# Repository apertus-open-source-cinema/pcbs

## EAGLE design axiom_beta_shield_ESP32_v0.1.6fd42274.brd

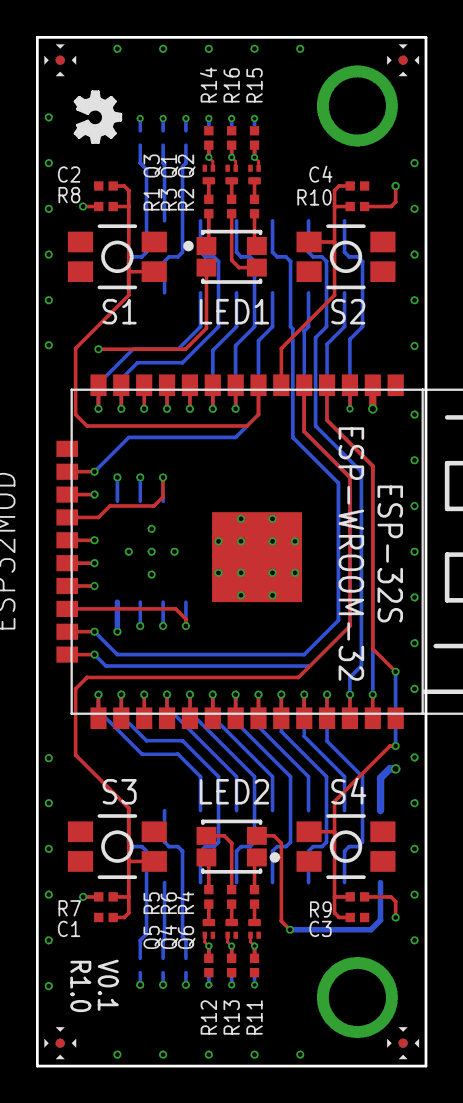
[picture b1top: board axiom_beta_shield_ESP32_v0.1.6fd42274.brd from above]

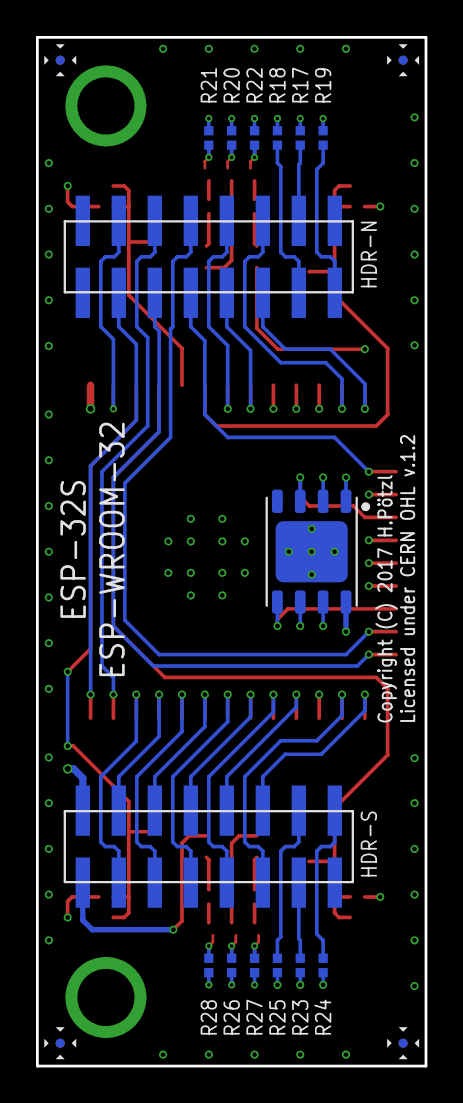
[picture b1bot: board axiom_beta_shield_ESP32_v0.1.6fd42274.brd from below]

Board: 4 copper layers, 21.6 x 57.1 mm, 49 parts (15 on the bottom side), 61 nets.

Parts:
C1, C2, C3, C4: 0402-C
HDR-N: 2X08M_SMD
HDR-S: 2X08M_SMD
LED1, LED2: RGBLED_PLCC4
LOGO1: OSHW_LOGO_FILLX0100-NT; OSHW_FILLX100_NOTEXT
Q1, Q2, Q3, Q4, Q5, Q6: PMZB290UNE; SOT883(B)
R1, R2, R3, R4, R5, R6, R7, R8, R9, R10, R11, R12, R13, R14, R15, R16, R17, R18, R19, R20, R21, R22, R23, R24, R25, R26, R27, R28: 0402-C
S1, S2, S3, S4: DTSM-6; 3X4MM
U1: ESP32MOD
U$1: IS25LP128; WSON127P600X500-8N

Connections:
B1: Q1.3, R3.1
B2: Q4.3, R6.1
G1: Q2.3, R2.1
G2: Q5.3, R5.1
GND: C1.2, C2.2, C3.2, C4.2, HDR-N.1, HDR-N.2, Q1.2, Q2.2, Q3.2, Q4.2, Q5.2, Q6.2, R11.1, R12.1, R13.1, R14.1, R15.1, R16.1, S1.1, S2.1, S3.1, S4.1, U1.0, U1.1, U1.15, U1.38, U$1.4, U$1.PAD
LED1_B: R20.2, U1.11
LED1_G: R21.2, U1.12
LED1_R: R22.2, U1.10
LED2_R: R28.2, U1.27
unnamed: LED1.1, R1.2
unnamed: LED1.4, R2.2
unnamed: LED1.3, R3.2
unnamed: LED2.1, R4.2
unnamed: LED2.4, R5.2
unnamed: LED2.3, R6.2
unnamed: Q3.1, R14.2, R19.1, R22.1
unnamed: Q2.1, R15.2, R18.1, R21.1
unnamed: Q1.1, R16.2, R17.1, R20.1
unnamed: Q4.1, R13.2, R23.1, R26.1
unnamed: Q5.1, R12.2, R24.1, R27.1
unnamed: Q6.1, R11.2, R25.1, R28.1
R1: Q3.3, R1.1
R2: Q6.3, R4.1
S1: C2.1, R8.1, S1.4, U1.7
S2: C4.1, R10.1, S2.4, U1.6
S3: C1.1, R7.1, S3.4, U1.5
S4: C3.1, R9.1, S4.4, U1.4
SH_N_IO0: HDR-N.12, U1.13
SH_N_IO1: HDR-N.11, U1.14
SH_N_IO2: HDR-N.10, U1.8
SH_N_IO3: HDR-N.9, U1.9
SH_N_IO4: HDR-N.8, U1.23
SH_N_IO5: HDR-N.7, U1.16
SH_N_IO6: HDR-N.6, U1.36
SH_N_IO7: HDR-N.5, U1.24
SH_N_IO8: HDR-N.4, U1.3
SH_N_IO9: HDR-N.3, R27.2, U1.37
SH_S_IO0: HDR-S.12, U1.25
SH_S_IO1: HDR-S.11, U1.26
SH_S_IO2: HDR-S.10, R26.2, U1.28
SH_S_IO3: HDR-S.9, U1.29
SH_S_IO4: HDR-S.8, U1.30
SH_S_IO5: HDR-S.7, U1.31
SH_S_IO6: HDR-S.6, U1.32
SH_S_IO7: HDR-S.5, U1.33
SH_S_IO8: HDR-S.4, U1.34
SH_S_IO9: HDR-S.3, U1.35
SPI: U1.22, U$1.5
SPICLK: U1.20, U$1.6
SPICS0: U1.19, U$1.1
SPIHD: U1.17, U$1.7
SPIQ: U1.21, U$1.2
SPIWP: U1.18, U$1.3
VCC: HDR-S.2, R7.2, R8.2, R9.2, R10.2, U1.2, U$1.8
VDD: HDR-S.1, LED1.2, LED2.2
XX1_N: HDR-N.14, R17.2
XX2_N: HDR-N.13, R18.2
XX2_P: HDR-N.15, R19.2
XX3_P: HDR-S.13, R23.2
XX4_N: HDR-S.16, R24.2
XX4_P: HDR-S.14, R25.2

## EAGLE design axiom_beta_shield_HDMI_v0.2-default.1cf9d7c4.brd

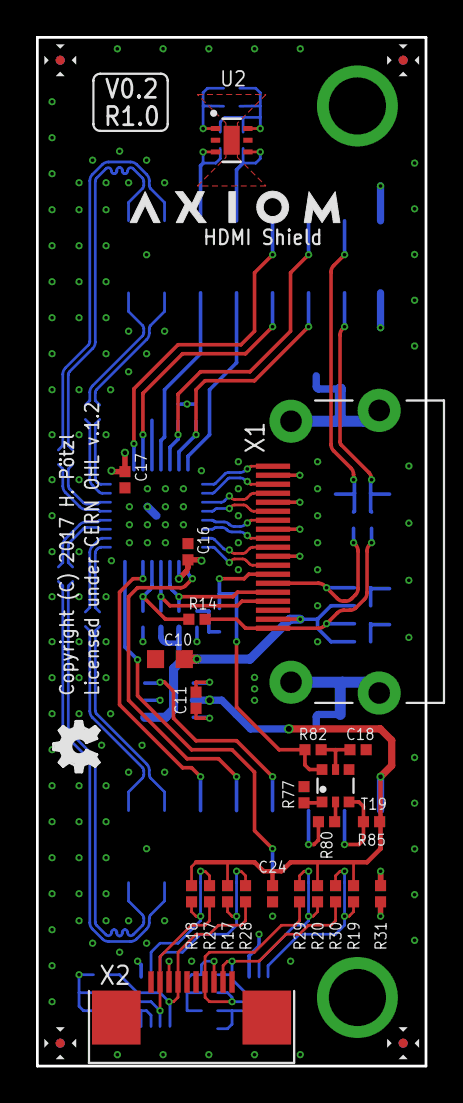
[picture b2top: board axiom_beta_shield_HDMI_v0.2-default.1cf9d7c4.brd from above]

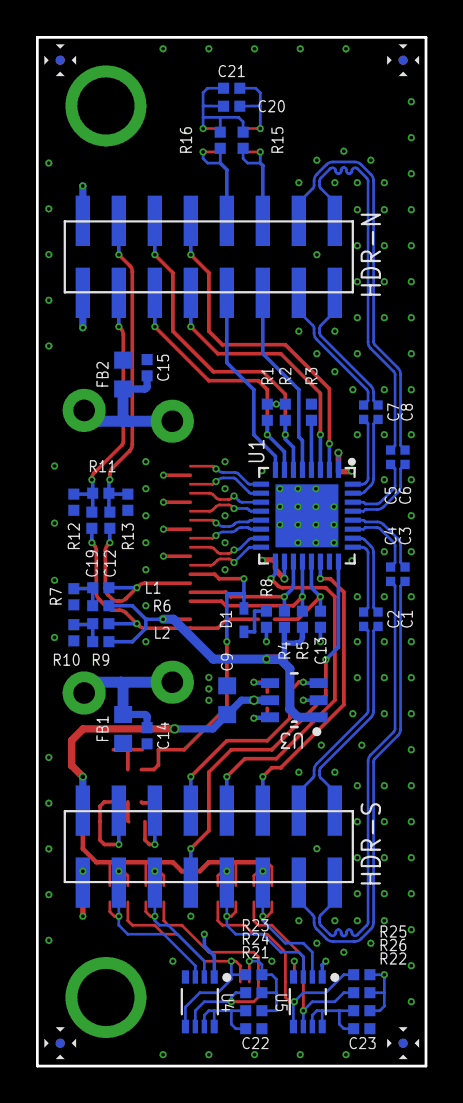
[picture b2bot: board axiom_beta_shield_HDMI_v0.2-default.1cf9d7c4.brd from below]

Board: 4 copper layers, 21.6 x 57.1 mm, 76 parts (50 on the bottom side), 73 nets.

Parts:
C1, C2, C3, C4, C5, C6, C7, C8: 100n; 0402-C
C9: 2u2; 0603-B
C10: 10u; 0603-B
C11: 220n; 0402-B
C12, C19: 0402-B
C13: 1-10n; 0402-B
C14, C15: 10n; 0402-B
C16, C17, C20, C22, C23: 100n; 0402-B
C18: 47p; 0402-B
C21, C24: 10u; 0402-B
D1: SOD523
FB1, FB2: 0603-B
HDR-N: 2X08M_SMD
HDR-S: 2X08M_SMD
L1, L2: 0402-B
LOGO1: OSHW_LOGO_FILLX0100-NT; OSHW_FILLX100_NOTEXT
R1, R2, R4, R5: 2k2; 0402-B
R3: 12k4; 0402-B
R6, R7, R8, R9, R10, R11, R12, R13, R14: 0402-B
R15, R16: 1k; 0402-B
R17, R18, R19, R20, R21, R22, R23, R24, R25, R26: 4k7; 0402-B
R27, R28, R29, R30: 100R; 0402-B
R31: 0R; 0402-B
R77: 100; 0402-B
R80: 10k; 0402-B
R82: 1M; 0402-B
R85: 100k; 0402-B
T19: PMBT3904SY; SOT363
U1: PTN3363; HVQFN32
U2: NOA1305; CUDFN6
U3: REG710-DBV; DBV
U4, U5: GTL2002DC; VSSOP-8
U$1: AXIOM_LOGO459X70; AXIOM_LOGO_459X70
X1: HDMI-10029449; 10029449-X01XLF
X2: 68711014022

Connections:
3V3: C9.1, C16.1, C17.1, C20.1, C21.1, C24.1, HDR-S.2, R1.1, R2.1, R8.1, R15.1, R16.1, R17.1, R18.1, R19.1, R20.1, R85.2, U1.1, U1.18, U2.6, U3.5, U4.1, U5.1
5V0: C10.1, R4.1, R5.1, R6.1, R9.1, U3.1, X1.18
CLOCK_N: U1.16, X1.12
CLOCK_P: U1.15, X1.10
DATA0_N: U1.14, X1.9
DATA0_P: U1.13, X1.7
DATA1_N: U1.12, X1.6
DATA1_P: U1.11, X1.4
DATA2_N: U1.10, X1.3
DATA2_P: U1.9, X1.1
GND: C9.2, C10.2, C13.2, C14.2, C15.2, C16.2, C17.2, C18.2, C20.2, C21.2, C22.2, C23.2, C24.2, FB1.2, FB2.2, HDR-N.1, HDR-N.2, R3.2, R7.2, R10.2, R12.2, R13.2, R77.1, T19.4, U1.EP, U2.1, U3.2, U4.4, U5.4, X1.2, X1.5, X1.8, X1.11, X1.17, X2.1, X2.5, X2.6, X2.10
HDMI_CEC: D1.C, R82.2, T19.6, X1.13
HDMI_SCL: R4.2, U1.19, X1.15
HDMI_SDA: R5.2, U1.20, X1.16
HEAC+: C12.1, L1.1, X1.14
HEAC-: C19.1, L2.1, R14.2, X1.19
HPD: C13.1, R14.1, U1.21
IN_D1_N: C2.1, U1.25
IN_D1_P: C1.1, U1.26
IN_D2_N: C4.1, U1.27
IN_D2_P: C3.1, U1.28
IN_D3_N: C6.1, U1.29
IN_D3_P: C5.1, U1.30
IN_D4_N: C8.1, U1.31
IN_D4_P: C7.1, U1.32
unnamed: L1.2, R6.2, R7.1
unnamed: L2.2, R9.2, R10.1
unnamed: C22.1, R21.2, U4.7, U4.8
unnamed: C23.1, R22.2, U5.7, U5.8
unnamed: C15.1, FB2.1, X1.Z3, X1.Z4
unnamed: C11.1, U3.6
unnamed: C11.2, U3.4
unnamed: C14.1, FB1.1, X1.Z1, X1.Z2
unnamed: R3.1, U1.4
unnamed: D1.A, R8.2
unnamed: R77.2, T19.1
unnamed: C18.1, R82.1, T19.5
unnamed: R80.1, T19.2
SH_N_IO0: HDR-N.12, R15.2, U2.3
SH_N_IO1: HDR-N.11, U1.5
SH_N_IO2: HDR-N.10, R16.2, U2.4
SH_N_IO3: HDR-N.9, U1.8
SH_N_IO4: HDR-N.8, U1.2
SH_N_IO5: HDR-N.7, U1.3
SH_N_IO6: HDR-N.6, R2.2, U1.6
SH_N_IO7: HDR-N.5, R1.2, U1.7
SH_N_IO8: C12.2, HDR-N.4, R11.1, R13.1
SH_N_IO9: C19.2, HDR-N.3, R11.2, R12.1
SH_S_IO0: HDR-S.12, U1.22
SH_S_IO1: HDR-S.11, R18.2, R27.1, U5.2
SH_S_IO2: HDR-S.10, U1.17
SH_S_IO3: HDR-S.9, R17.2, R28.1, U5.3
SH_S_IO4: HDR-S.8, U3.3
SH_S_IO5: HDR-S.7, U1.24
SH_S_IO6: HDR-S.6, R80.2
SH_S_IO7: HDR-S.5, R20.2, R29.1, U4.2
SH_S_IO8: HDR-S.4, R85.1, T19.3
SH_S_IO9: HDR-S.3, R19.2, R30.1, U4.3
S_IO1: R26.2, R27.2, U5.6, X2.2
S_IO3: R25.2, R28.2, U5.5, X2.4
S_IO7: R24.2, R29.2, U4.6, X2.7
S_IO9: R23.2, R30.2, U4.5, X2.9
VDD: HDR-S.1, R31.2
VIO13: R22.1, R25.1, R26.1, X2.3
VIO79: R21.1, R23.1, R24.1, R31.1, X2.8
XX1_N: C6.2, HDR-N.14
XX1_P: C5.2, HDR-N.16
XX2_N: C7.2, HDR-N.13
XX2_P: C8.2, HDR-N.15
XX3_N: C4.2, HDR-S.15
XX3_P: C3.2, HDR-S.13
XX4_N: C1.2, HDR-S.16
XX4_P: C2.2, HDR-S.14

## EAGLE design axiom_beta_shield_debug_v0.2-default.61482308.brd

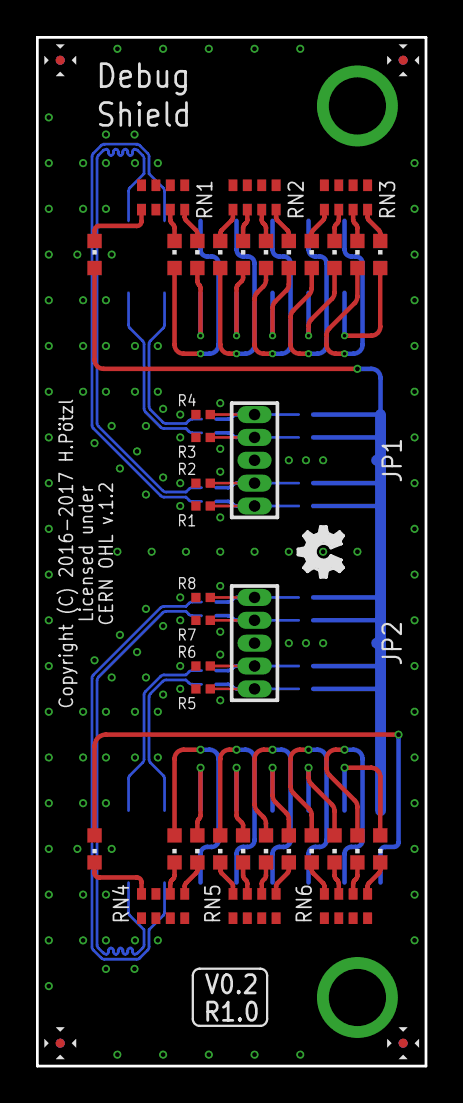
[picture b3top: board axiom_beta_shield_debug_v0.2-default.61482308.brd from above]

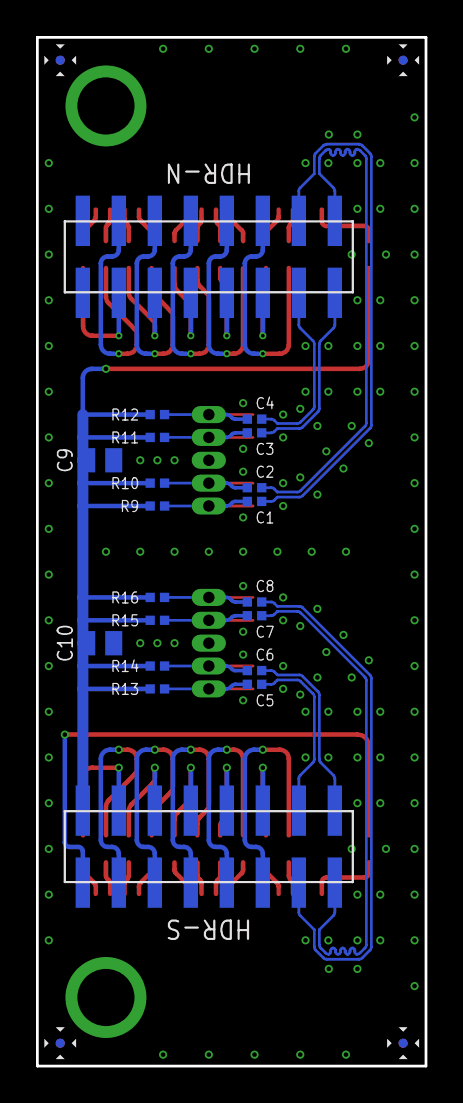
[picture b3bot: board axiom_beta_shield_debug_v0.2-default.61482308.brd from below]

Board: 4 copper layers, 21.6 x 57.1 mm, 59 parts (20 on the bottom side), 61 nets.

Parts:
C1, C2, C3, C4, C5, C6, C7, C8: 0402-C
C9, C10: 0805-C
HDR-N: 2X08M_SMD
HDR-S: 2X08M_SMD
JP1, JP2: 1X05U
LED1, LED2, LED3, LED4, LED5, LED6, LED7, LED8, LED9, LED10, LED11, LED12, LED13, LED14, LED15, LED16, LED17, LED18, LED19, LED20, LED21, LED22: CHIPLED_0603
LOGO1: OSHW_LOGO_FILLX0100-NT; OSHW_FILLX100_NOTEXT
R1, R2, R3, R4, R5, R6, R7, R8, R9, R10, R11, R12, R13, R14, R15, R16: 0402-C
RN1, RN2, RN3, RN4, RN5, RN6: CAY16

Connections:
GND: C9.2, C10.2, HDR-N.1, HDR-N.2, JP1.3, JP2.3, R1.2, R2.2, R3.2, R4.2, R5.2, R6.2, R7.2, R8.2, RN1.1, RN1.2, RN1.4, RN2.1, RN2.2, RN2.3, RN2.4, RN3.1, RN3.2, RN3.3, RN3.4, RN4.1, RN4.3, RN4.4, RN5.1, RN5.2, RN5.3, RN5.4, RN6.1, RN6.2, RN6.3, RN6.4
unnamed: LED20.C, RN6.5
unnamed: LED19.C, RN6.6
unnamed: LED18.C, RN6.7
unnamed: LED17.C, RN6.8
unnamed: LED16.C, RN5.5
unnamed: LED15.C, RN5.6
unnamed: LED14.C, RN5.7
unnamed: LED13.C, RN5.8
unnamed: LED12.C, RN4.5
unnamed: LED11.C, RN4.6
unnamed: LED3.C, RN2.5
unnamed: LED4.C, RN2.6
unnamed: LED5.C, RN2.7
unnamed: LED6.C, RN2.8
unnamed: LED7.C, RN3.5
unnamed: LED8.C, RN3.6
unnamed: LED9.C, RN3.7
unnamed: LED10.C, RN3.8
unnamed: LED1.C, RN1.7
unnamed: LED2.C, RN1.8
unnamed: C1.2, JP1.1, R1.1, R9.2
unnamed: C2.2, JP1.2, R2.1, R10.2
unnamed: C3.2, JP1.4, R3.1, R11.2
unnamed: C4.2, JP1.5, R4.1, R12.2
unnamed: C5.2, JP2.1, R5.1, R13.2
unnamed: C6.2, JP2.2, R6.1, R14.2
unnamed: LED21.C, RN1.5
unnamed: C7.2, JP2.4, R7.1, R15.2
unnamed: C8.2, JP2.5, R8.1, R16.2
unnamed: LED22.C, RN4.8
SH_N_IO0: HDR-N.12, LED1.A
SH_N_IO1: HDR-N.11, LED2.A
SH_N_IO2: HDR-N.10, LED3.A
SH_N_IO3: HDR-N.9, LED4.A
SH_N_IO4: HDR-N.8, LED5.A
SH_N_IO5: HDR-N.7, LED6.A
SH_N_IO6: HDR-N.6, LED7.A
SH_N_IO7: HDR-N.5, LED8.A
SH_N_IO8: HDR-N.4, LED9.A
SH_N_IO9: HDR-N.3, LED10.A
SH_S_IO0: HDR-S.12, LED11.A
SH_S_IO1: HDR-S.11, LED12.A
SH_S_IO2: HDR-S.10, LED13.A
SH_S_IO3: HDR-S.9, LED14.A
SH_S_IO4: HDR-S.8, LED15.A
SH_S_IO5: HDR-S.7, LED16.A
SH_S_IO6: HDR-S.6, LED17.A
SH_S_IO7: HDR-S.5, LED18.A
SH_S_IO8: HDR-S.4, LED19.A
SH_S_IO9: HDR-S.3, LED20.A
VCC: C9.1, C10.1, HDR-S.2, LED21.A, R9.1, R10.1, R11.1, R12.1, R13.1, R14.1, R15.1, R16.1
VDD: HDR-S.1, LED22.A
XX1_N: C1.1, HDR-N.14
XX1_P: C2.1, HDR-N.16
XX2_N: C4.1, HDR-N.13
XX2_P: C3.1, HDR-N.15
XX3_N: C7.1, HDR-S.15
XX3_P: C8.1, HDR-S.13
XX4_N: C6.1, HDR-S.16
XX4_P: C5.1, HDR-S.14

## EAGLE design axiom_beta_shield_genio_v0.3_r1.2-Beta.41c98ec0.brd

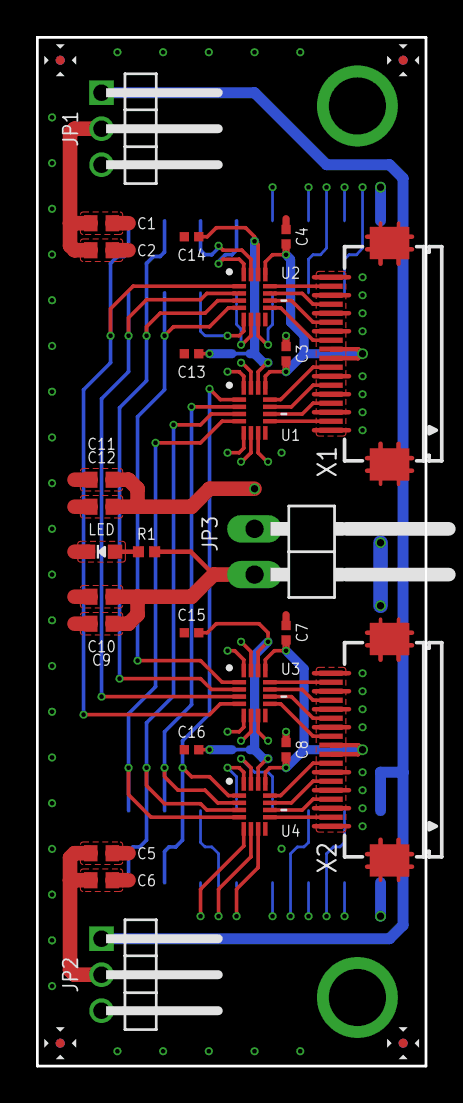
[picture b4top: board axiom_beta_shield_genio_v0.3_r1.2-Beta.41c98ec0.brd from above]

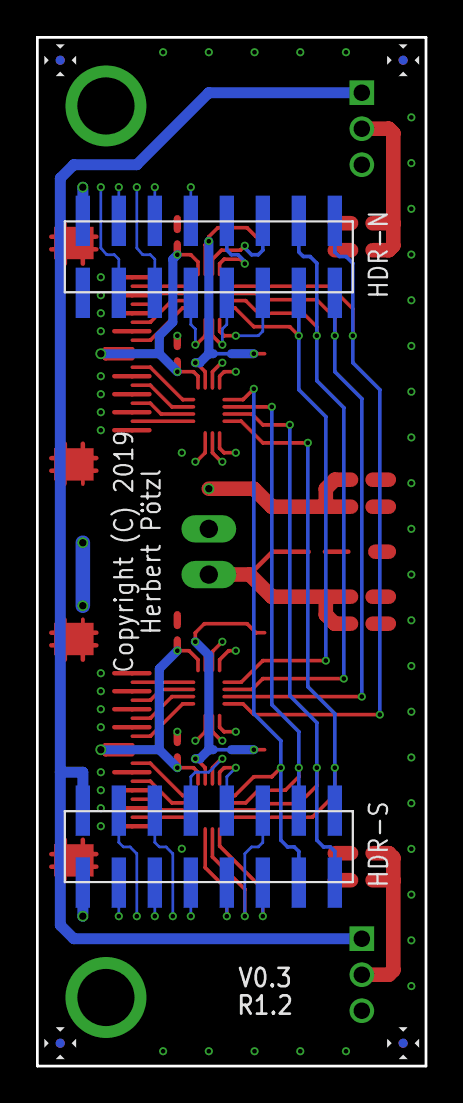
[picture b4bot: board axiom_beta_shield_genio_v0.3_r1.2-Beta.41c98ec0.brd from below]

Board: 4 copper layers, 21.6 x 57.1 mm, 29 parts (2 on the bottom side), 51 nets.

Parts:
C1, C2, C5, C6, C9, C10, C11, C12: 0603-C
C3, C4, C7, C8, C13, C14, C15, C16: 0402-C
HDR-N: 2X08M_SMD
HDR-S: 2X08M_SMD
JP1, JP2: 1X03M/90-S
JP3: 1X02/90
LED: CHIPLED_0603_NOOUTLINE
R1: 10k; 0402-B
U1, U2, U3, U4: SN74AVC4T774RSV; QFN40P185X265X55-16N
X1, X2: FH12-18S-0.5SH

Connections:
0CH1: U1.9, X1.2
0CH2: U1.10, X1.4
0CH3: U1.11, X1.6
0CH4: U1.12, X1.8
0CH5: U2.9, X1.11
0CH6: U2.10, X1.13
0CH7: U2.11, X1.15
0CH8: U2.12, X1.17
0VCC: C1.1, C2.1, C3.1, C4.1, JP1.2, U1.13, U2.13, X1.9, X1.10
1CH1: U4.9, X2.2
1CH2: U4.10, X2.4
1CH3: U4.11, X2.6
1CH4: U4.12, X2.8
1CH5: U3.9, X2.11
1CH6: U3.10, X2.13
1CH7: U3.11, X2.15
1CH8: U3.12, X2.17
1VCC: C5.1, C6.1, C7.1, C8.1, JP2.2, U3.13, U4.13, X2.9, X2.10
3V3: HDR-S.2, JP1.1, JP2.1
GND: C1.2, C2.2, C3.2, C4.2, C5.2, C6.2, C7.2, C8.2, C9.2, C10.2, C11.2, C12.2, C13.2, C14.2, C15.2, C16.2, HDR-N.1, HDR-N.2, JP3.1, LED.C, U1.8, U2.8, U3.8, U4.8, X1.1, X1.3, X1.5, X1.7, X1.12, X1.14, X1.16, X1.18, X2.1, X2.3, X2.5, X2.7, X2.12, X2.14, X2.16, X2.18
unnamed: LED.A, R1.2
SH_N_IO0: HDR-N.12, U2.15
SH_N_IO1: HDR-N.11, U2.5
SH_N_IO2: HDR-N.10, U2.16
SH_N_IO3: HDR-N.9, U2.6
SH_N_IO4: HDR-N.8, U1.15
SH_N_IO5: HDR-N.7, U2.7
SH_N_IO6: HDR-N.6, U1.16
SH_N_IO7: HDR-N.5, U1.5
SH_N_IO8: HDR-N.4, U1.6
SH_N_IO9: HDR-N.3, U1.7
SH_S_IO0: HDR-S.12, U4.6
SH_S_IO1: HDR-S.11, U4.5
SH_S_IO2: HDR-S.10, U4.16
SH_S_IO3: HDR-S.9, U4.7
SH_S_IO4: HDR-S.8, U4.15
SH_S_IO5: HDR-S.7, U3.7
SH_S_IO6: HDR-S.6, U3.6
SH_S_IO7: HDR-S.5, U3.5
SH_S_IO8: HDR-S.4, U3.16
SH_S_IO9: HDR-S.3, U3.15
VCCIO: C11.1, C12.1, C13.1, C14.1, C15.1, C16.1, HDR-S.1, U1.14, U2.14, U3.14, U4.14
VIN: C9.1, C10.1, JP1.3, JP2.3, JP3.2, R1.1
XX1_N: HDR-N.14, U2.3, U3.2
XX1_P: HDR-N.16, U2.1, U3.4
XX2_N: HDR-N.13, U2.4, U3.1
XX2_P: HDR-N.15, U2.2, U3.3
XX3_N: HDR-S.15, U1.3, U4.3
XX3_P: HDR-S.13, U1.1, U4.1
XX4_N: HDR-S.16, U1.4, U4.4
XX4_P: HDR-S.14, U1.2, U4.2

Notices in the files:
axiom_beta_shield_ESP32_v0.1.6fd42274.brd:
Copyright (C) 2017 H.Pötzl
Licensed under CERN OHL v.1.2
axiom_beta_shield_debug_v0.2-default.61482308.brd:
Copyright (C) 2016-2017 H.Pötzl
CERN OHL v.1.2
axiom_beta_shield_genio_v0.3_r1.2-Beta.41c98ec0.brd:
Copyright (C) 2019
parts and their libraries:
microbuilder: This work is placed in the public domain, and may be freely used for commercial and non-commercial work with the following conditions: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
eiCan_03_ZIF_Connectors_Flat_Flexible_Ca: Copyright: Würth Elektronik
